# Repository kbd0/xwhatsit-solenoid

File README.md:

# xwhatsit-solenoid

Combination of purdeaandrei's universal xwhatsit: https://github.com/purdeaandrei/SMDModelFController

and solenoid driver: https://github.com/purdeaandrei/SolenoidDriver

into one PCB.
 
Not compatible with 3178
 
Original licensure holds

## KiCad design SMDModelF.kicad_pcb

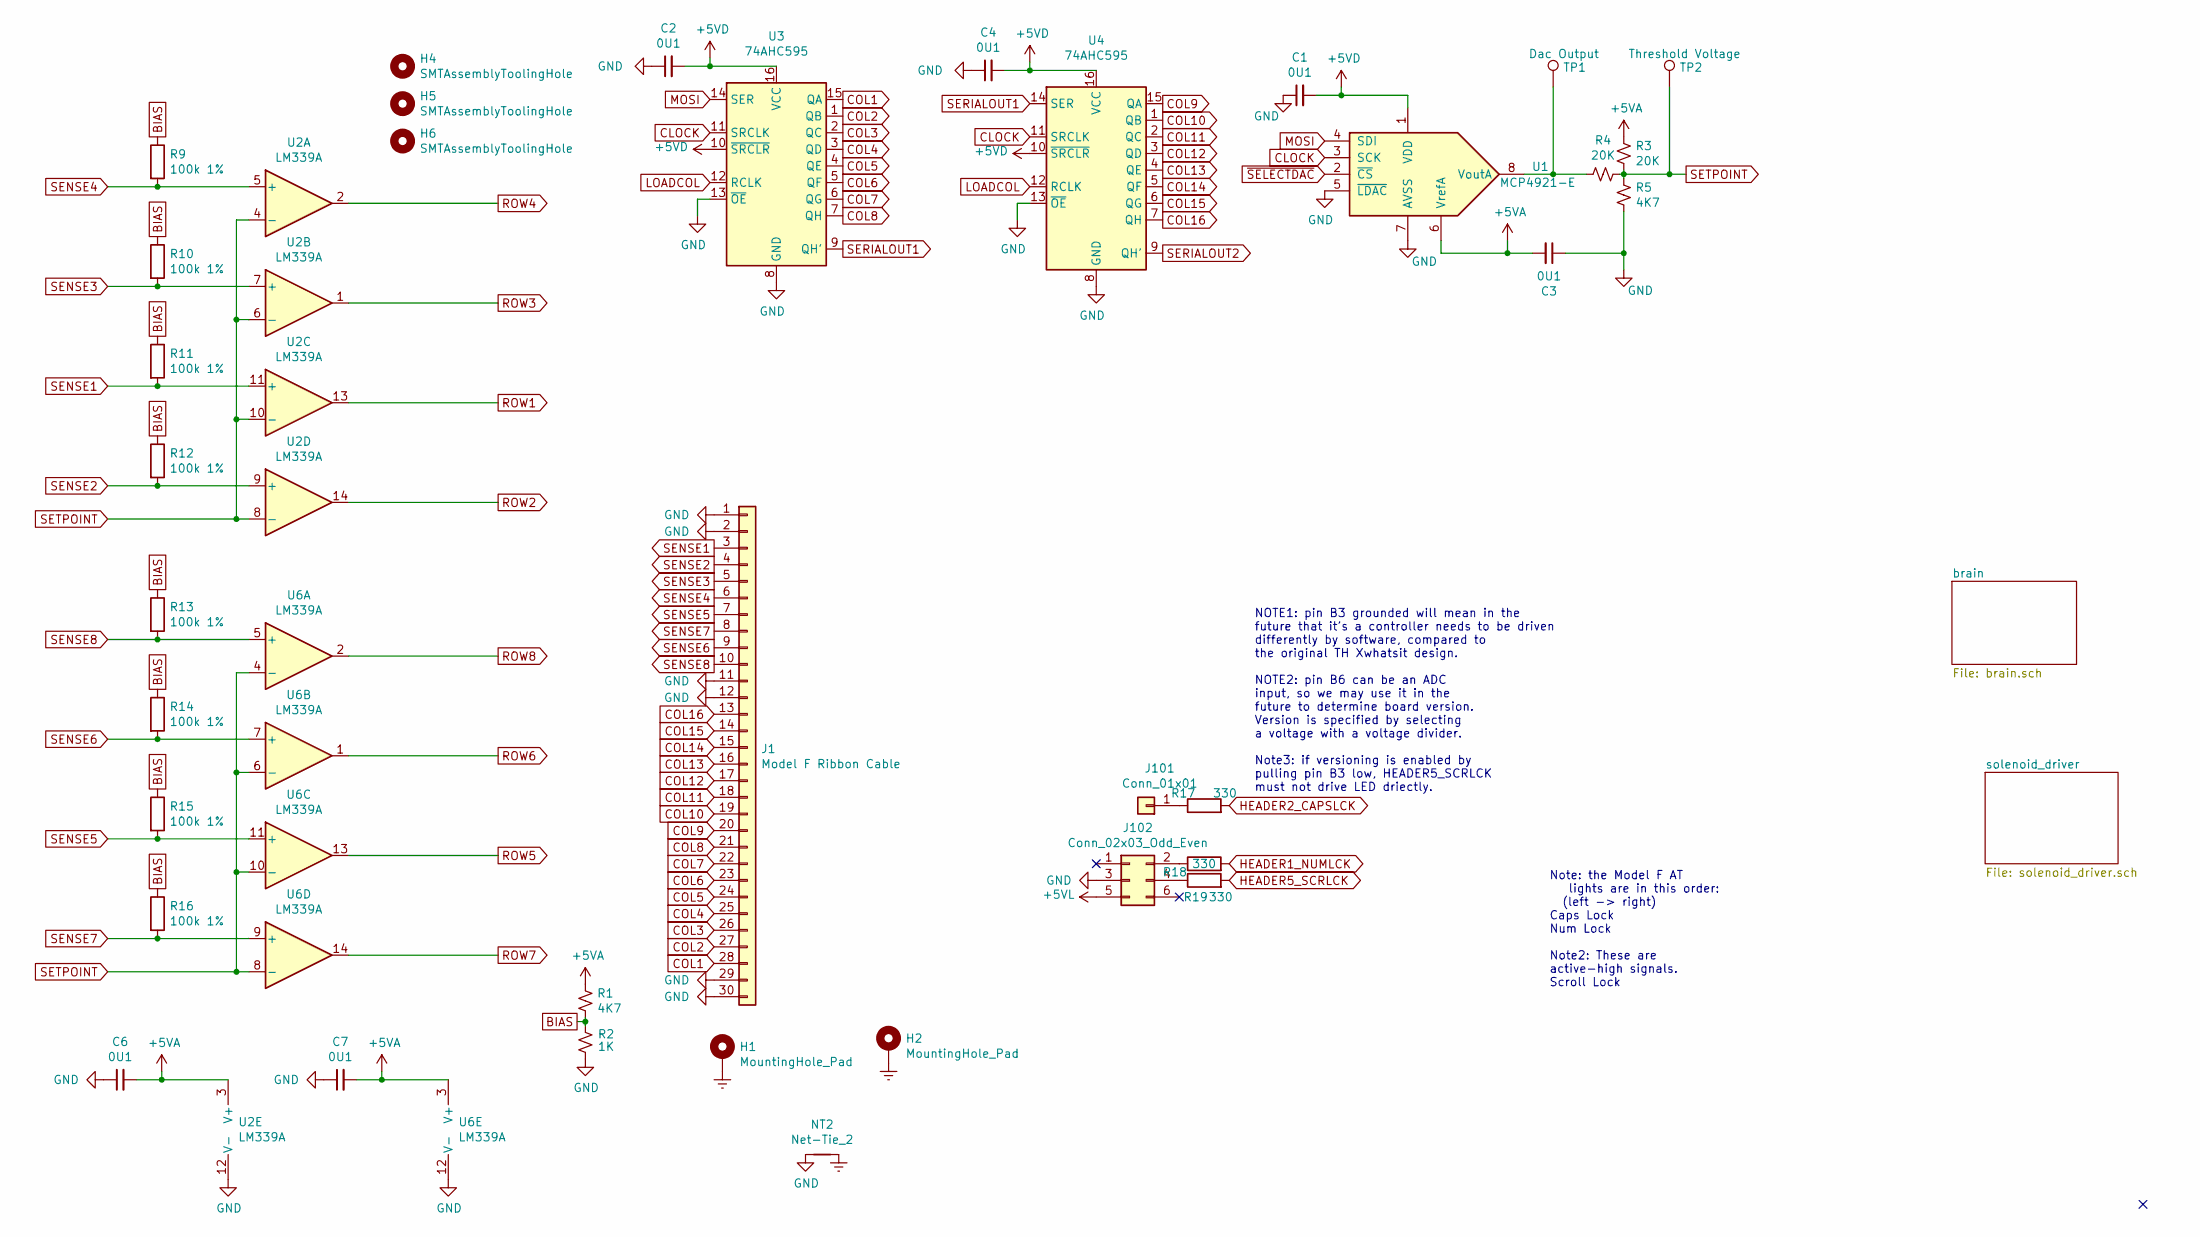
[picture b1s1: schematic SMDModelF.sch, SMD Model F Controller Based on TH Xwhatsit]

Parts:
C1, C2, C3, C4, C6, C7: 0U1; C_0805_2012Metric_Pad1.15x1.40mm_HandSolder; LCSC C49678
H1: MountingHole_Pad; ModelF_new_mounting_hole_left
H2: MountingHole_Pad; ModelF_new_mounting_hole_right
H4, H5, H6: SMTAssemblyToolingHole; tooling_hole
J1: Model F Ribbon Cable; Model_F_3.96mm_pitch_footprint
J101: Conn_01x01; PinHeader_1x01_P2.54mm_Horizontal; LCSC C2883798
J102: Conn_02x03_Odd_Even; PinHeader_2x03_P2.54mm_Horizontal; LCSC C239334
NT2: Net-Tie_2; NetTie-2_SMD_Pad0.5mm
R1, R5: 4K7; R_0805_2012Metric_Pad1.15x1.40mm_HandSolder; LCSC C17673
R2: 1K; R_0805_2012Metric_Pad1.15x1.40mm_HandSolder; LCSC C17513
R3, R4: 20K; R_0805_2012Metric_Pad1.15x1.40mm_HandSolder; LCSC C4328
R9, R10, R11, R12, R13, R14, R15, R16: 100k 1%; R_0805_2012Metric_Pad1.15x1.40mm_HandSolder; LCSC C17407
R17, R18, R19: 330; R_0805_2012Metric_Pad1.15x1.40mm_HandSolder; LCSC C17630
TP1: Dac Output; TestPoint_Pad_D1.0mm
TP2: Threshold Voltage; TestPoint_Pad_D1.0mm
U1: MCP4921-E; SOIC-8_3.9x4.9mm_P1.27mm; LCSC C43499
U2, U6: LM339A; SOIC-14_3.9x8.7mm_P1.27mm; LCSC C74559
U3, U4: 74AHC595; SOIC-16_3.9x9.9mm_P1.27mm; LCSC C5520

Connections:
+5VA: C3.2, C6.2, C7.2, R1.1, R3.2, U1.6 (VrefA), U2.3 (V+), U6.3 (V+); also elsewhere on the board
+5VD: C1.2, C2.2, C4.2, U1.1 (VDD), U3.10 (~SRCLR), U3.16 (VCC), U4.10 (~SRCLR), U4.16 (VCC); also elsewhere on the board
BIAS: R1.2, R2.2, R9.1, R10.1, R11.1, R12.1, R13.1, R14.1, R15.1, R16.1
CLOCK: U1.3 (SCK), U3.11 (SRCLK), U4.11 (SRCLK); also elsewhere on the board
COL1: J1.28, U3.15 (QA)
COL2: J1.27, U3.1 (QB)
COL3: J1.26, U3.2 (QC)
COL4: J1.25, U3.3 (QD)
COL5: J1.24, U3.4 (QE)
COL6: J1.23, U3.5 (QF)
COL7: J1.22, U3.6 (QG)
COL8: J1.21, U3.7 (QH)
COL9: J1.20, U4.15 (QA)
COL10: J1.19, U4.1 (QB)
COL11: J1.18, U4.2 (QC)
COL12: J1.17, U4.3 (QD)
COL13: J1.16, U4.4 (QE)
COL14: J1.15, U4.5 (QF)
COL15: J1.14, U4.6 (QG)
COL16: J1.13, U4.7 (QH)
Earth: H1.1, H2.1, NT2.2; also elsewhere on the board
GND: C1.1, C2.1, C3.1, C4.1, C6.1, C7.1, J1.1, J1.2, J1.11, J1.12, J1.29, J1.30, J102.3, NT2.1, R2.1, R5.1, U1.5 (~LDAC~), U1.7 (AVSS), U2.12 (V-), U3.8 (GND), U3.13 (~OE), U4.8 (GND), U4.13 (~OE), U6.12 (V-); also elsewhere on the board
HEADER1_NUMLCK: R18.2; also elsewhere on the board
HEADER2_CAPSLCK: R17.2; also elsewhere on the board
HEADER5_SCRLCK: R19.2; also elsewhere on the board
LOADCOL: U3.12 (RCLK), U4.12 (RCLK); also elsewhere on the board
MOSI: U1.4 (SDI), U3.14 (SER); also elsewhere on the board
unnamed 43: J101.1, R17.1; also elsewhere on the board
unnamed 45: J102.2, R18.1; also elsewhere on the board
unnamed 46: J102.4, R19.1; also elsewhere on the board
unnamed: R4.2, TP1.1, U1.8 (VoutA)
ROW1: U2.13; also elsewhere on the board
ROW2: U2.14; also elsewhere on the board
ROW3: U2.1; also elsewhere on the board
ROW4: U2.2; also elsewhere on the board
ROW5: U6.13; also elsewhere on the board
ROW6: U6.1; also elsewhere on the board
ROW7: U6.14; also elsewhere on the board
ROW8: U6.2; also elsewhere on the board
SENSE1: J1.3, R11.2, U2.11 (+)
SENSE2: J1.4, R12.2, U2.9 (+)
SENSE3: J1.5, R10.2, U2.7 (+)
SENSE4: J1.6, R9.2, U2.5 (+)
SENSE5: J1.7, R15.2, U6.11 (+)
SENSE6: J1.9, R14.2, U6.7 (+)
SENSE7: J1.8, R16.2, U6.9 (+)
SENSE8: J1.10, R13.2, U6.5 (+)
SERIALOUT1: U3.9 (QH'), U4.14 (SER)
SERIALOUT2: U4.9 (QH')
SETPOINT: R3.1, R4.1, R5.2, TP2.1, U2.4 (-), U2.6 (-), U2.8 (-), U2.10 (-), U6.4 (-), U6.6 (-), U6.8 (-), U6.10 (-)
~SELECTDAC: U1.2 (~CS~); also elsewhere on the board

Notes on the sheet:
Note: the Model F AT lights are in this order: (left -> right) Caps Lock Num Lock Note2: These are active-high signals. Scroll Lock
NOTE1: pin B3 grounded will mean in the future that it's a controller needs to be driven differently by software, compared to the original TH Xwhatsit design. NOTE2: pin B6 can be an ADC input, so we may use it in the future to determine board version. Version is specified by selecting a voltage wi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

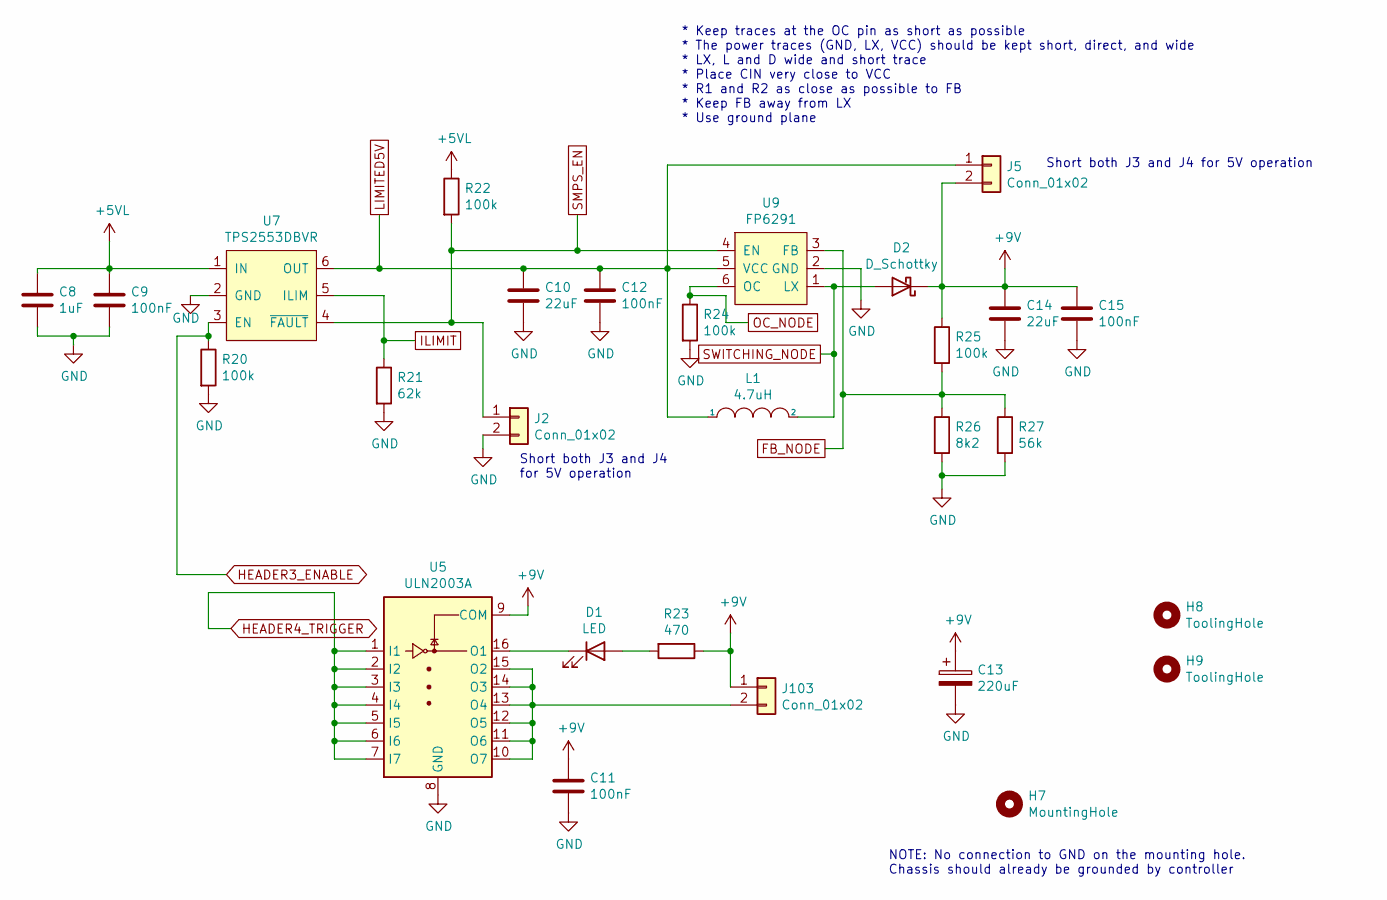
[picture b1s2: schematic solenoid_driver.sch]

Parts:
C8: 1uF; C_0805_2012Metric_Pad1.15x1.40mm_HandSolder; LCSC C28323
C9, C11, C12, C15: 100nF; C_0805_2012Metric_Pad1.15x1.40mm_HandSolder; LCSC C49678
C10, C14: 22uF; C_0603_1608Metric_Pad1.05x0.95mm_HandSolder; LCSC C45783
C13: 220uF; CP_Elec_6.3x7.7; LCSC C127327
D1: LED; LED_0805_2012Metric_Pad1.15x1.40mm_HandSolder; LCSC C2296
D2: D_Schottky; D_SMA; LCSC C2480
H7: MountingHole; MountingHole_4mm_Pad
H8, H9: ToolingHole; tooling_hole
J2, J5: Conn_01x02; shortable
J103: Conn_01x02; PinHeader_1x02_P2.54mm_Horizontal; LCSC C2905424
L1: 4.7uH; footprint_for_MWSA0503_HANDSOLD; LCSC C408410
R20, R22, R24, R25: 100k; R_0805_2012Metric_Pad1.15x1.40mm_HandSolder; LCSC C17407
R21: 62k; R_0805_2012Metric_Pad1.15x1.40mm_HandSolder; LCSC C17783
R23: 470; R_0805_2012Metric_Pad1.15x1.40mm_HandSolder; LCSC C17710
R26: 8k2; R_0805_2012Metric_Pad1.15x1.40mm_HandSolder; LCSC C17828
R27: 56k; R_0805_2012Metric_Pad1.15x1.40mm_HandSolder; LCSC C17756
U5: ULN2003A; SOIC-16_3.9x9.9mm_P1.27mm; LCSC C7512
U7: TPS2553DBVR; SOT-23-6_Handsoldering; LCSC C55266
U9: FP6291; SOT-23-6_Handsoldering; LCSC C18701

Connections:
+5VL: C8.1, C9.1, R22.1, U7.1 (IN); also elsewhere on the board
+9V: C11.1, C13.1, C14.1, C15.1, D2.1 (K), J5.2, J103.1, R23.1, R25.1, U5.9 (COM); also elsewhere on the board
FB_NODE: R25.2, R26.1, R27.1, U9.3 (FB)
GND: C8.2, C9.2, C10.2, C11.2, C12.2, C13.2, C14.2, C15.2, J2.2, R20.2, R21.2, R24.2, R26.2, R27.2, U5.8 (GND), U7.2 (GND), U9.2 (GND); also elsewhere on the board
HEADER3_ENABLE: R20.1, U7.3 (EN); also elsewhere on the board
HEADER4_TRIGGER: U5.1 (I1), U5.2 (I2), U5.3 (I3), U5.4 (I4), U5.5 (I5), U5.6 (I6), U5.7 (I7); also elsewhere on the board
ILIMIT: R21.1, U7.5 (ILIM)
LIMITED5V: C10.1, C12.1, J5.1, L1.1, U7.6 (OUT), U9.5 (VCC)
unnamed: D1.1 (K), U5.16 (O1)
unnamed: D1.2 (A), R23.2
unnamed 42: J103.2, U5.10 (O7), U5.11 (O6), U5.12 (O5), U5.13 (O4), U5.14 (O3), U5.15 (O2); also elsewhere on the board
OC_NODE: R24.1, U9.6 (OC)
SMPS_EN: J2.1, R22.2, U7.4 (~FAULT), U9.4 (EN)
SWITCHING_NODE: D2.2 (A), L1.2, U9.1 (LX)

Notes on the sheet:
* Keep traces at the OC pin as short as possible * The power traces (GND, LX, VCC) should be kept short, direct, and wide * LX, L and D wide and short trace * Place CIN very close to VCC * R1 and R2 as close as possible to FB * Keep FB away from LX * Use ground plane
NOTE: No connection to GND on the mounting hole. Chassis should already be grounded by controller
Short both J3 and J4 for 5V operation
Short both J3 and J4 for 5V operation

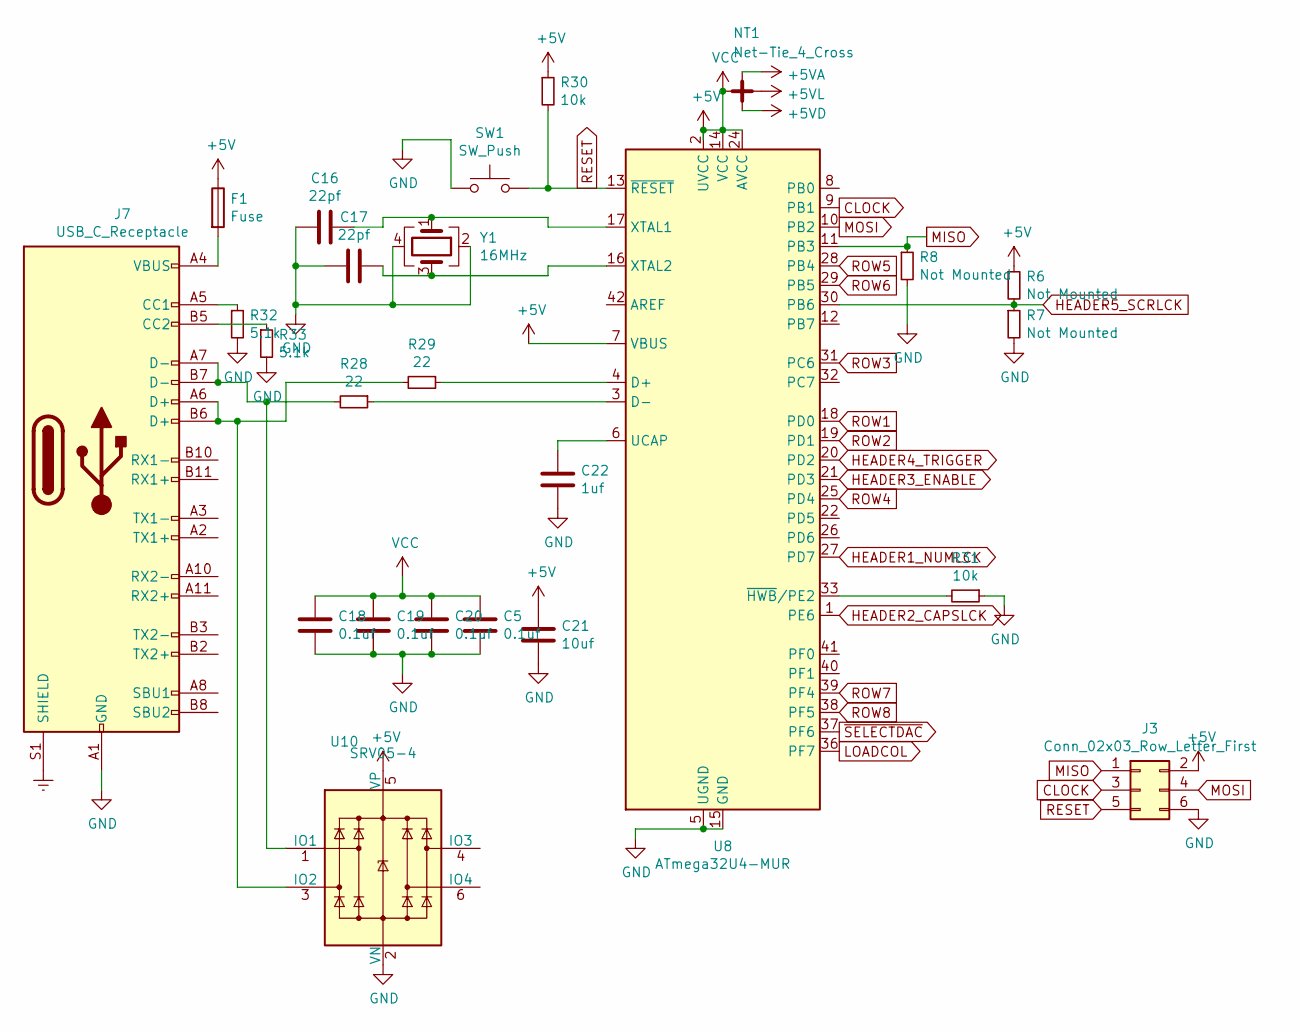
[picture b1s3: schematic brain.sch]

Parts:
C5, C18, C19, C20: 0.1uf; C_0805_2012Metric_Pad1.15x1.40mm_HandSolder
C16, C17: 22pf; C_0805_2012Metric_Pad1.15x1.40mm_HandSolder
C21: 10uf; C_0805_2012Metric_Pad1.15x1.40mm_HandSolder
C22: 1uf; C_0805_2012Metric_Pad1.15x1.40mm_HandSolder
F1: Fuse; Fuse_0805_2012Metric_Castellated
J3: Conn_02x03_Row_Letter_First; PinHeader_2x03_P2.54mm_Vertical
J7: USB_C_Receptacle; USB_C_Receptacle_XKB_U262-16XN-4BVC11
NT1: Net-Tie_4_Cross; NetTie-2_THT_Pad1.0mm
R6, R7, R8: Not Mounted; R_0805_2012Metric_Pad1.15x1.40mm_HandSolder
R28, R29: 22; R_0805_2012Metric_Pad1.15x1.40mm_HandSolder
R30, R31: 10k; R_0805_2012Metric_Pad1.15x1.40mm_HandSolder
R32, R33: 5.1k; R_0805_2012Metric
SW1: SW_Push; SW_TS-1187A-B-A-B
U8: ATmega32U4-MUR; TQFP-44_10x10mm_P0.8mm
U10: SRV05-4; SOT-23-6
Y1: 16MHz; OSC_X322516MLB4SI

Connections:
+5V: C5.2, C18.2, C19.2, C20.2, C21.2, F1.1, J3.2, NT1.1, R6.1, R30.1, U8.2 (UVCC), U8.7 (VBUS), U8.14 (VCC), U8.24 (AVCC), U8.34 (VCC), U8.44 (AVCC), U10.5 (VP)
+5VA: NT1.3; also elsewhere on the board
+5VD: NT1.4; also elsewhere on the board
+5VL: NT1.2; also elsewhere on the board
CLOCK: J3.3, U8.9 (PB1); also elsewhere on the board
Earth: J7.S1 (SHIELD); also elsewhere on the board
GND: C5.1, C16.2, C17.2, C18.1, C19.1, C20.1, C21.1, C22.1, J3.6, J7.A1 (GND), J7.A12 (GND), J7.B1 (GND), J7.B12 (GND), R7.2, R8.2, R31.1, R32.2, R33.2, SW1.1, U8.5 (UGND), U8.15 (GND), U8.23 (GND), U8.35 (GND), U8.43 (GND), U8.45 (GND), U10.2 (VN), Y1.2, Y1.4; also elsewhere on the board
HEADER1_NUMLCK: U8.27 (PD7); also elsewhere on the board
HEADER2_CAPSLCK: U8.1 (PE6); also elsewhere on the board
HEADER3_ENABLE: U8.21 (PD3); also elsewhere on the board
HEADER4_TRIGGER: U8.20 (PD2); also elsewhere on the board
HEADER5_SCRLCK: R6.2, R7.1, U8.30 (PB6); also elsewhere on the board
LOADCOL: U8.36 (PF7); also elsewhere on the board
MISO: J3.1, R8.1, U8.11 (PB3)
MOSI: J3.4, U8.10 (PB2); also elsewhere on the board
unnamed: C16.1, U8.17 (XTAL1), Y1.1
unnamed: C17.1, U8.16 (XTAL2), Y1.3
unnamed: C22.2, U8.6 (UCAP)
unnamed: F1.2, J7.A4 (VBUS), J7.A9 (VBUS), J7.B4 (VBUS), J7.B9 (VBUS)
unnamed: J7.A5 (CC1), R32.1
unnamed: J7.A6 (D+), J7.B6 (D+), R29.2, U10.3 (IO2)
unnamed: J7.A7 (D-), J7.B7 (D-), R28.2, U10.1 (IO1)
unnamed: J7.B5 (CC2), R33.1
unnamed: R28.1, U8.3 (D-)
unnamed: R29.1, U8.4 (D+)
unnamed: R31.2, U8.33 (~HWB~/PE2)
RESET: J3.5, R30.2, SW1.2, U8.13 (~RESET)
ROW1: U8.18 (PD0); also elsewhere on the board
ROW2: U8.19 (PD1); also elsewhere on the board
ROW3: U8.31 (PC6); also elsewhere on the board
ROW4: U8.25 (PD4); also elsewhere on the board
ROW5: U8.28 (PB4); also elsewhere on the board
ROW6: U8.29 (PB5); also elsewhere on the board
ROW7: U8.39 (PF4); also elsewhere on the board
ROW8: U8.38 (PF5); also elsewhere on the board
~SELECTDAC: U8.37 (PF6); also elsewhere on the board

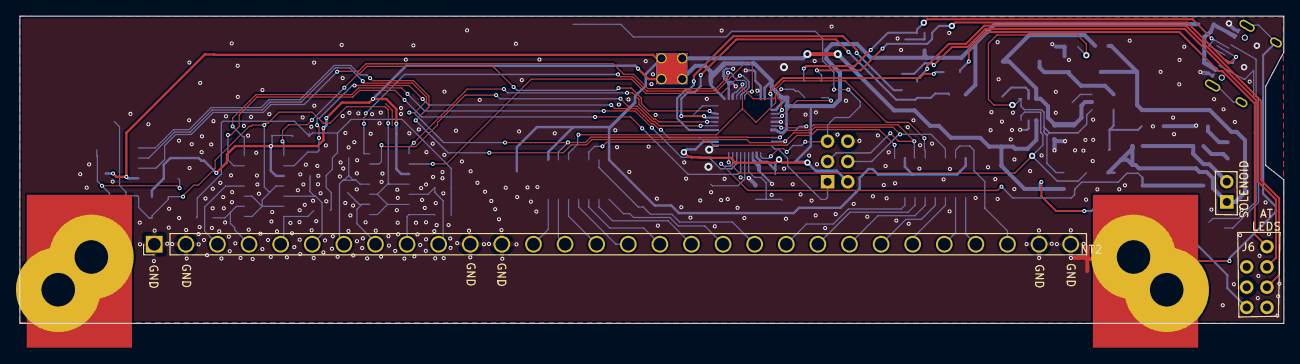
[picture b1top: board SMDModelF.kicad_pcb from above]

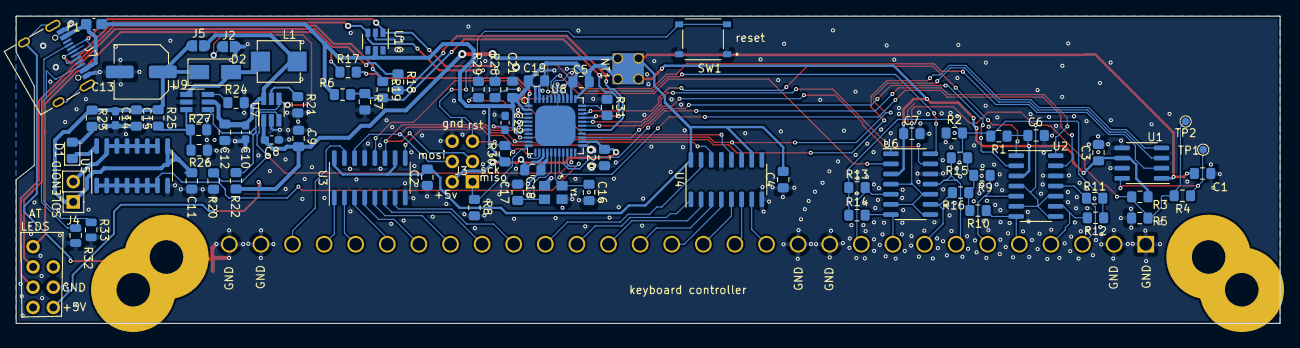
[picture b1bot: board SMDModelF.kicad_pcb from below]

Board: 2 copper layers, 158.4 x 38.5 mm, 84 parts (79 on the bottom side), 77 nets.

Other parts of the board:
J4: Conn_01x02; PinHeader_1x02_P2.54mm_Vertical
J6: MODEL F AT LOCKLIGHTS HEADER; FAT_LockLightsConnector

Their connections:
+5VL: J6.7; also elsewhere on the board
+9V: J4.1; also elsewhere on the board
GND: J6.5; also elsewhere on the board
unnamed 42: J4.2; also elsewhere on the board
unnamed 43: J6.2; also elsewhere on the board
unnamed 45: J6.4; also elsewhere on the board
unnamed 46: J6.6; also elsewhere on the board

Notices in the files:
SMDModelF.kicad_pcb:
Licenced under CERN OHL Version 1.2
Copyright Rainy Day Plans.
This documentation describes Open Hardware and is licensed under the
CERN OHL v. 1.2.
